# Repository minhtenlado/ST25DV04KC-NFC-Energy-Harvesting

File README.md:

<div align="center">

# NFC LED — Battery-Free Energy Harvesting PCB

**A working, credit-card-sized NFC circuit powered directly by a smartphone's 13.56 MHz magnetic field.**

No battery · No USB power · No microcontroller firmware · Custom PCB spiral antenna

<sub>Actual fabricated PCB — not a rendering.</sub>

[**▶ Live GIF demo**](#-live-hardware-demonstration) · [**Photos**](#-real-hardware--gallery) · [**Hardware**](#-hardware-overview) · [**PCB coil settings**](#-pcb-coil-creator-settings) · [**First-time ST25 setup**](#-first-time-st25-nfc-tap-configuration) · [**Manufacturing**](#-manufacturing-files)

</div>

---

## ✨ Project overview

**NFC LED** is a standalone, battery-free electronics project built around the **STMicroelectronics ST25DV04KC-JF6L3**, a miniature NFC Forum Type 5 dynamic tag with an **energy-harvesting output (`V_EH`)**.

A planar spiral coil etched directly into the PCB captures energy from the NFC field generated by a compatible smartphone or reader. When energy harvesting is enabled and the available RF power is sufficient, the IC makes harvested power available at `V_EH`, allowing **two on-board LEDs** to illuminate without an external supply.

The PCB has been **fabricated, assembled and successfully tested**. This repository contains the editable KiCad project, 3D model, actual PCB photos, an animated hardware demonstration and production exports.

### Highlights

- **Zero external power:** no battery, charging circuit or wired power supply.
- **Tiny NFC IC:** ST25DV04KC-JF6L3, **WLCSP-10** package.
- **Integrated antenna:** approximately nine-turn circular copper spiral on the PCB.
- **Two visible LEDs:** a simple, immediate demonstration of harvested RF energy.
- **Reproducible design files:** KiCad schematic, PCB, 3D model, and Gerber/drill exports.
- **Smartphone configuration:** set the nonvolatile ST25 energy-harvesting mode through the **ST25 NFC Tap** Android app; no firmware flashing required.

> **Important:** The board demonstrates **NFC energy harvesting**. It is not a wireless-charging module capable of delivering arbitrary power: the LEDs depend on reader power, placement, coupling, and the configured harvesting mode.

## 🎬 Live Hardware Demonstration

<div align="center">

### Battery-Free NFC LED — Real Hardware Demo

<sub>Real hardware demonstration · NFC energy harvesting at 13.56 MHz · Battery-free LED operation</sub>

</div>

## 📸 Real hardware & gallery

### Fabricated PCB — both sides

<table>
  <tr>
    <td width="50%" align="center"></td>
    <td width="50%" align="center"></td>
  </tr>
  <tr>
    <td align="center"><sub>Real PCB — front / antenna side</sub></td>
    <td align="center"><sub>Real PCB — back / artwork side</sub></td>
  </tr>
</table>

### KiCad 3D renders

<table>
  <tr>
    <td width="50%" align="center"></td>
    <td width="50%" align="center"></td>
  </tr>
  <tr>
    <td align="center"><sub>3D — component / top side</sub></td>
    <td align="center"><sub>3D — reverse side</sub></td>
  </tr>
</table>

### Copper layout and schematic

<div align="center">
  
  <br />
  <sub>Schematic: NFC coil → ST25DV04KC energy harvesting → two LED branches.</sub>
</div>

[View the original schematic PDF](schematic.pdf) · [Open the KiCad schematic](NFC_LED_ST25DV.kicad_sch) · [Open the PCB layout](NFC_LED_ST25DV.kicad_pcb)

## 🔌 Hardware overview

| Item | Specification / implementation |
| :-- | :-- |
| Main NFC IC | **ST25DV04KC-JF6L3** — 4 Kbit dynamic NFC tag, WLCSP-10 |
| Wireless interface | **13.56 MHz**, ISO/IEC 15693, NFC Forum Type 5 |
| Antenna | PCB-etched, circular spiral coil |
| Coil construction | 9 turns, single copper layer; routed to the IC with a return connection |
| LEDs | **2 × 0603 SMD red LEDs** (`LED1`, `LED2`) |
| LED current limiting | **2 × 47 Ω** (`R1`, `R2`), one resistor per LED |
| Decoupling | **100 nF** (`C1`) on the harvested-energy output |
| Power rail | `V_EH` from ST25DV04KC (no external supply) |
| PCB | **2 copper layers**, approximately **85.6 × 54 mm**, 1.6 mm nominal thickness |
| Design software | KiCad |
| Operating principle | **RF field → coil → ST25DV energy harvesting → LED load** |

### Circuit operation

```text
         NFC-enabled smartphone / RFID reader
                       │
                13.56 MHz RF field
                       │
           Custom circular PCB antenna
                       │ AC0 / AC1
              ST25DV04KC-JF6L3
                       │ V_EH
             ┌─────────┼──────────┐
             │         │          │
          C1 100nF   R1 47Ω     R2 47Ω
             │         │          │
             │        LED1       LED2
             │         │          │
             └─────────┴──────────┘
                       │
                      GND
```

`V_EH` is an **unregulated** output. LED brightness and power availability vary with the RF reader, antenna alignment, separation, coupling and load. Avoid assuming a fixed output voltage.

## 🌀 PCB Coil Creator settings

This project's antenna was designed with a **circular spiral PCB coil generator**.

| Generator setting | Value used |
| :-- | :-- |
| Footprint name | `COIL_GENERATOR` |
| Layer count | `1` |
| Turns per layer | `9` |
| Outer diameter | `44 mm` |
| Turn direction | `clockwise` |
| Trace width | `0.50 mm` |
| Trace spacing | `0.36 mm` |
| Via outer diameter | `0.60 mm` |
| Via drill diameter | `0.30 mm` |

**Trace pitch:** `0.50 + 0.36 = 0.86 mm` between adjacent trace centerlines, as a nominal input setting.

### Generate or reproduce the antenna in KiCad

1. Install **[PCB Coil Creator](https://github.com/DIaLOGIKa-GmbH/kicad-coil-creator)** from KiCad's **Plugin and Content Manager** (KiCad 7 or newer) or install the plugin's release ZIP with **Install from File**.
2. Open **PCB Editor** and launch the coil tool from the external/add-on plugin area. Depending on the installed version, the dialog may be labelled **Coil Generator**.
3. Select a **circular coil** and enter the settings listed in the table; choose the **front copper** layer for the spiral.
4. Use **Generate Coil** to preview/place the geometry, or **Save as Project Footprint** to preserve it as a reusable footprint, where supported by the plugin.
5. Route the two coil terminals to the IC's `AC0` and `AC1`. Where necessary, use a short back-layer return connection and vias so traces do not cross on the same layer.
6. Check clearance, board-edge spacing, coil continuity and manufacturing limits in KiCad. Verify that large copper fills and metallic objects do not interfere with the coil.
7. **Do not assume the settings alone guarantee resonance at 13.56 MHz.** The actual inductance, total capacitance, resonance and performance depend on PCB stack-up and assembly; measure/tune the finished antenna when adapting the design.

> The screenshot above represents the **settings of this specific design**. Plugin appearance and exact control names can change between KiCad/plugin versions. The coil occupies one layer, while the **overall PCB is two-layer**.

## 📱 First-time ST25 NFC Tap configuration

**You do not flash MCU firmware to this board.** To enable the battery-free LED demonstration on a *new* ST25DV04KC device, configure its **nonvolatile energy-harvesting register** through the NFC interface.

### What you need

- Android phone with NFC enabled.
- **[ST25 NFC Tap — official Android app](https://play.google.com/store/apps/details?id=com.st.st25nfc)** by STMicroelectronics.
- Assembled NFC LED PCB; no battery or external supply.

### One-time setup

1. Turn on **NFC** in Android settings and open **ST25 NFC Tap** iOS does the same thing.
2. Hold the phone's NFC antenna close to the PCB spiral until the app detects the **ST25DV** tag (ISO/IEC 15693 / Type 5). The optimal phone position varies by model.
3. Open the app menu and enter **Register Management** (or the equivalent register/configuration screen in your app version).
4. Find the **static `EH_MODE`** configuration register (RF configuration register address **`0x02`**).
5. Set **`EH_MODE = 0x00`** — **energy harvesting enabled automatically after boot**, whenever sufficient RF power is present. Preserve other reserved bits and unrelated registers.
6. Press **Save / Write**. If the application asks for the **RF configuration password**, authenticate using the correct password for your tag. A factory-new, unmodified tag normally uses the default all-zero **64-bit** configuration password; do not assume this applies to a previously configured device.
7. Read back the register and confirm **`EH_MODE = 0x00`**. Remove the phone, then tap the PCB again to test power harvesting and LED illumination.

| Register / bit | Meaning |
| :-- | :-- |
| `EH_MODE = 0` (**static**, nonvolatile) | Enables automatic harvesting after boot when RF energy is sufficient |
| `EH_MODE = 1` (factory default) | On-demand harvesting; initially disabled after boot |
| `EH_EN` (**dynamic**) | Temporarily enable/disable energy harvesting without changing the saved default |
| `EH_ON` (**dynamic**, status) | Indicates whether the harvesting function is enabled |

**Why static `EH_MODE` matters:** Changing only the **dynamic `EH_EN`** bit can turn on energy harvesting for the current RF session, but it does **not** save the startup behavior for later taps. Set **static `EH_MODE = 0`** for this demonstration.

> **Troubleshooting:** If LEDs do not light, confirm the register was actually saved, try a different phone position and NFC antenna orientation, and ensure the phone maintains its NFC field. Harvesting may affect RF communication while the LEDs draw power. Some phones provide less power than others. Never change passwords or protection/lock settings unless you intend to manage them.

**ST documentation:** [ST25DV04KC datasheet](https://www.st.com/resource/en/datasheet/st25dv04kc.pdf) · [ST25 NFC Tap software](https://www.st.com/en/embedded-software/stsw-st25001.html) · [ST25 NFC Tap user manual (UM2131)](https://www.st.com/resource/en/user_manual/um2131-st25-android-nfc-tap-application-stmicroelectronics.pdf)

## 🏭 Manufacturing files

The `production/` folder contains fabrication and assembly exports supplied with this project.

| File | Use |
| :-- | :-- |
| [`production/NFC_LED_ST25DV.zip`](production/NFC_LED_ST25DV.zip) | Gerber layers, outline and drilling information for a PCB fabrication service |
| [`production/bom.csv`](production/bom.csv) | BOM / assembly export |
| [`production/positions.csv`](production/positions.csv) | Pick-and-place coordinates |
| [`production/designators.csv`](production/designators.csv) | Component designator export |
| [`production/netlist.ipc`](production/netlist.ipc) | IPC-format netlist export |

The manufacturing ZIP contains both copper Gerbers, mask/paste, silkscreen, outline and drill files. **Confirm BOM values and part sourcing independently before submitting another assembly order**: the existing BOM export has blank value/part-number columns, even though the KiCad schematic records the resistor and capacitor values.

### Reopen or customize in KiCad

1. Clone/download the repository.
2. Open `NFC_LED_ST25DV.kicad_pro` in KiCad.
3. Inspect `NFC_LED_ST25DV.kicad_sch` and `NFC_LED_ST25DV.kicad_pcb`.
4. The custom 3D IC model is included at [`library/ST25DV04KC-JF6L3.step`](library/ST25DV04KC-JF6L3.step); the board's model path is project-relative.
5. Re-run ERC/DRC and regenerate production files after changing the design. Recheck antenna tuning if you modify the coil, stack-up, copper thickness, or layout near it.

## 📂 Repository structure

```text
NFC_LED_ST25DV/
├── README.md
├── .gitignore
├── NFC_LED_ST25DV.kicad_pro
├── NFC_LED_ST25DV.kicad_sch
├── NFC_LED_ST25DV.kicad_pcb
├── schematic.pdf
├── images/
│   ├── Actual_photo(1).jpg
│   ├── Actual_photo(2).jpg
│   ├── board_3D.png
│   ├── board_3D_top.png
│   ├── board_3D_bottom.png
│   ├── Coil_creator.png
│   ├── Footprint.png
│   ├── schematic.png
│   └── NFC_LED_ST25DV_full_demo.gif
├── library/
│   └── ST25DV04KC-JF6L3.step
├── production/
│   ├── NFC_LED_ST25DV.zip
│   ├── bom.csv
│   ├── positions.csv
│   ├── designators.csv
│   └── netlist.ipc
```

KiCad local history (`.history/`), lock files and user-local `.kicad_prl` settings are excluded from the clean distribution; they are not required to manufacture or inspect the board.

## 🔗 References

- [ST25DV04KC official product page](https://www.st.com/en/nfc/st25dv04kc.html)
- [ST25DV04KC / ST25DV16KC / ST25DV64KC datasheet](https://www.st.com/resource/en/datasheet/st25dv04kc.pdf)
- [ST25 NFC Tap for Android](https://play.google.com/store/apps/details?id=com.st.st25nfc)
- [ST25 NFC Tap user manual](https://www.st.com/resource/en/user_manual/um2131-st25-android-nfc-tap-application-stmicroelectronics.pdf)
- [KiCad PCB Coil Creator plugin](https://github.com/DIaLOGIKa-GmbH/kicad-coil-creator)

---

<div align="center">

**Designed, fabricated & tested by Phan Huynh Van Do**

*Embedded hardware · PCB engineering · NFC energy harvesting*

</div>

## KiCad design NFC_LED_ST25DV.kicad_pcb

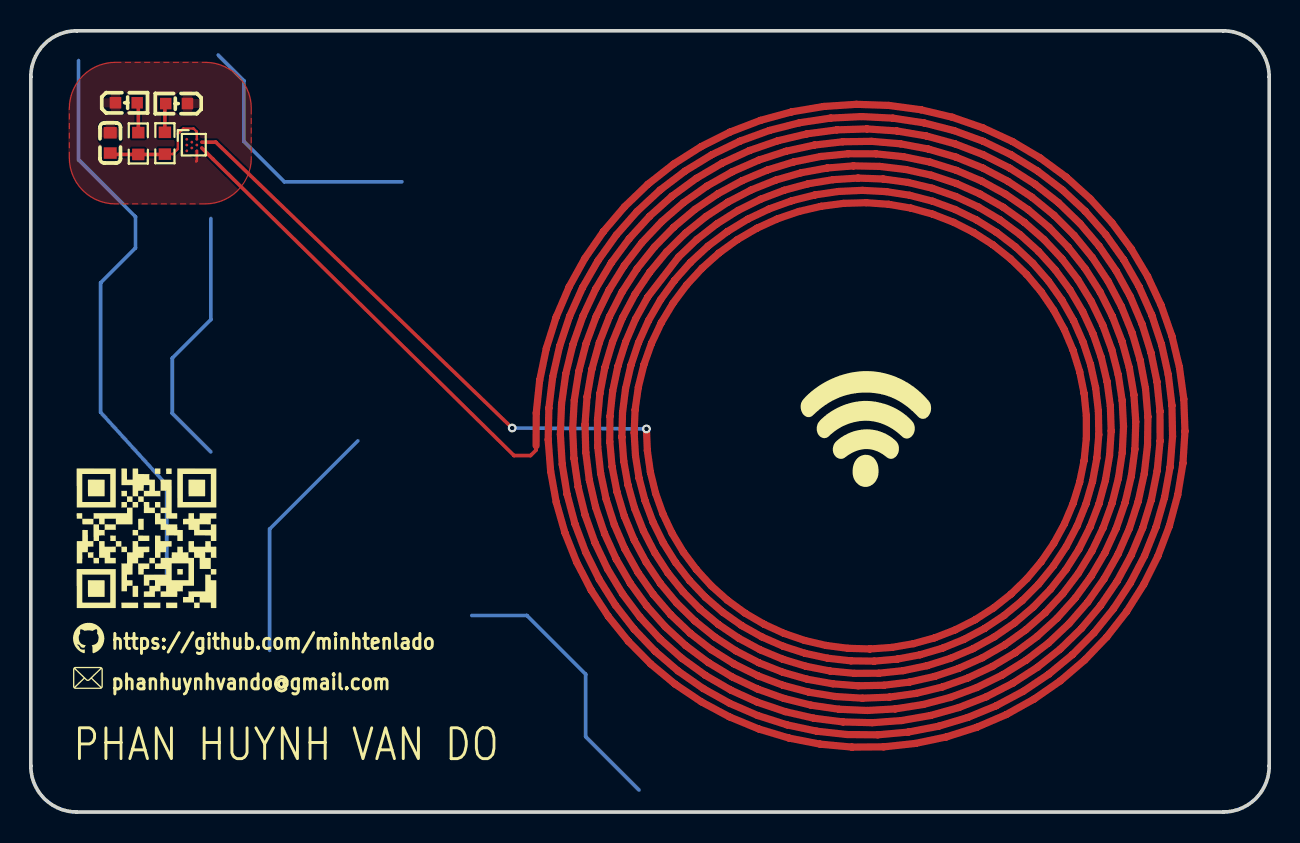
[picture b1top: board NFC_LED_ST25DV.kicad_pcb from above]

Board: 2 copper layers, 85.6 x 54.0 mm, 6 parts (0 on the bottom side), 5 nets.

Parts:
C1: C0603
LED1, LED2: LED-SMD_L1.6-W0.8-R-RD
R1, R2: R0603
U1: WLCSP-10_L1.7-W1.5-P0.50_ST_ST25DVXX

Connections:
$1N9: C1.2, R1.2, R2.2, U1.A3
$1N10: LED2.1, R2.1
$1N11: LED1.1, R1.1
ANT2: U1.B4, U1.D4
GND: C1.1, LED1.2, LED2.2, U1.E3
